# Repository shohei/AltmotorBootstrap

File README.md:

# Altmotor
## Schematics

## Artwork

## Implementation

##Test

## Excitation

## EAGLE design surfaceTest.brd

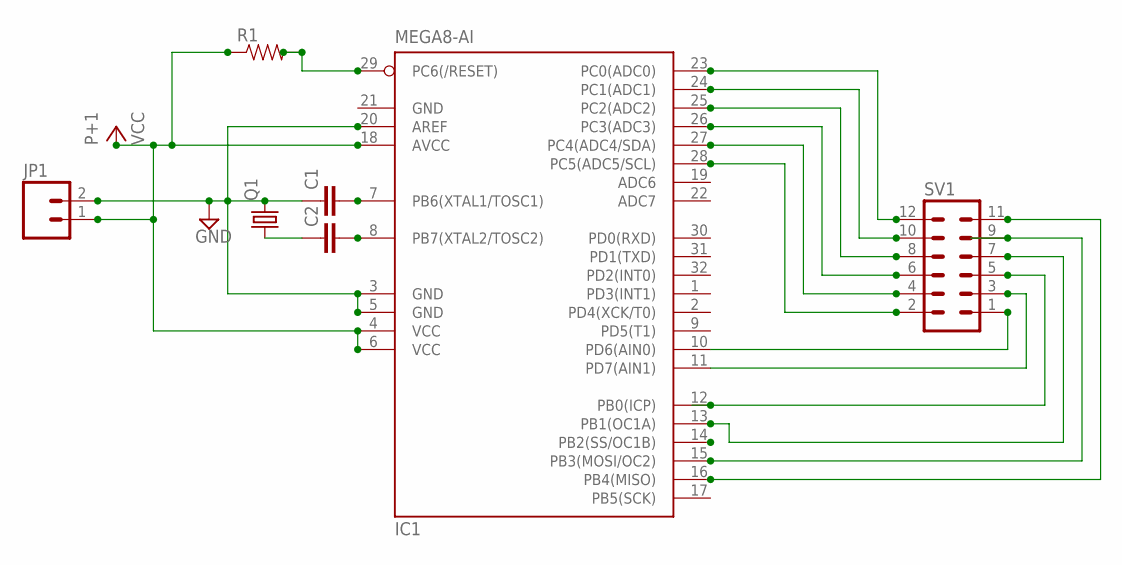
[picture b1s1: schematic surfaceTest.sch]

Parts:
C1, C2: CAPPTH1; CAP-PTH-5MM
IC1: MEGA8-AI; TQFP32-08
JP1: M02LOCK_LONGPADS; 1X02_LOCK_LONGPADS
Q1: CRYSTALHC18U-V; HC18U-V
R1: RESISTORAXIAL-0.3; AXIAL-0.3
SV1: MA06-2

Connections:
GND: C1.1, IC1.3 (GND), IC1.5 (GND), IC1.20 (AREF), IC1.21 (GND), JP1.2, Q1.2
unnamed: C1.2, IC1.7 (PB6(XTAL1/TOSC1))
unnamed: C2.2, IC1.8 (PB7(XTAL2/TOSC2))
unnamed: IC1.25 (PC2(ADC2)), SV1.8
unnamed: C2.1, Q1.1
unnamed: IC1.23 (PC0(ADC0)), SV1.12
unnamed: IC1.24 (PC1(ADC1)), SV1.10
unnamed: IC1.26 (PC3(ADC3)), SV1.6
unnamed: IC1.27 (PC4(ADC4/SDA)), SV1.4
unnamed: IC1.28 (PC5(ADC5/SCL)), SV1.2
unnamed: IC1.10 (PD6(AIN0)), SV1.1
unnamed: IC1.11 (PD7(AIN1)), SV1.3
unnamed: IC1.12 (PB0(ICP)), SV1.5
unnamed: IC1.13 (PB1(OC1A)), SV1.7
unnamed: IC1.15 (PB3(MOSI/OC2)), SV1.9
unnamed: IC1.16 (PB4(MISO)), SV1.11
unnamed: IC1.29 (PC6(/RESET)), R1.P$2 (2)
VCC: IC1.4 (VCC), IC1.6 (VCC), IC1.18 (AVCC), JP1.1, R1.P$1 (1)

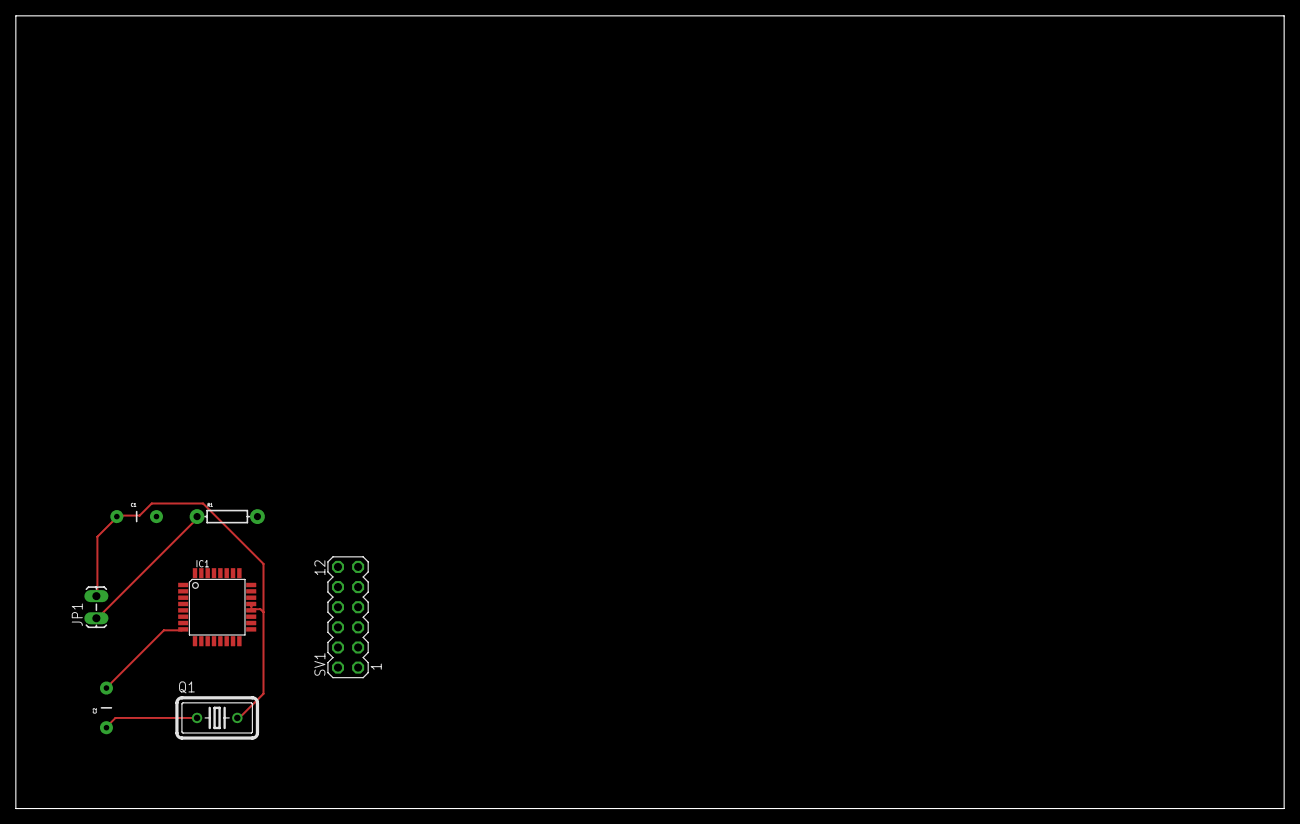
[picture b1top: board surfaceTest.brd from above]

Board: 2 copper layers, 160.0 x 100.0 mm, 7 parts (0 on the bottom side), 18 nets.

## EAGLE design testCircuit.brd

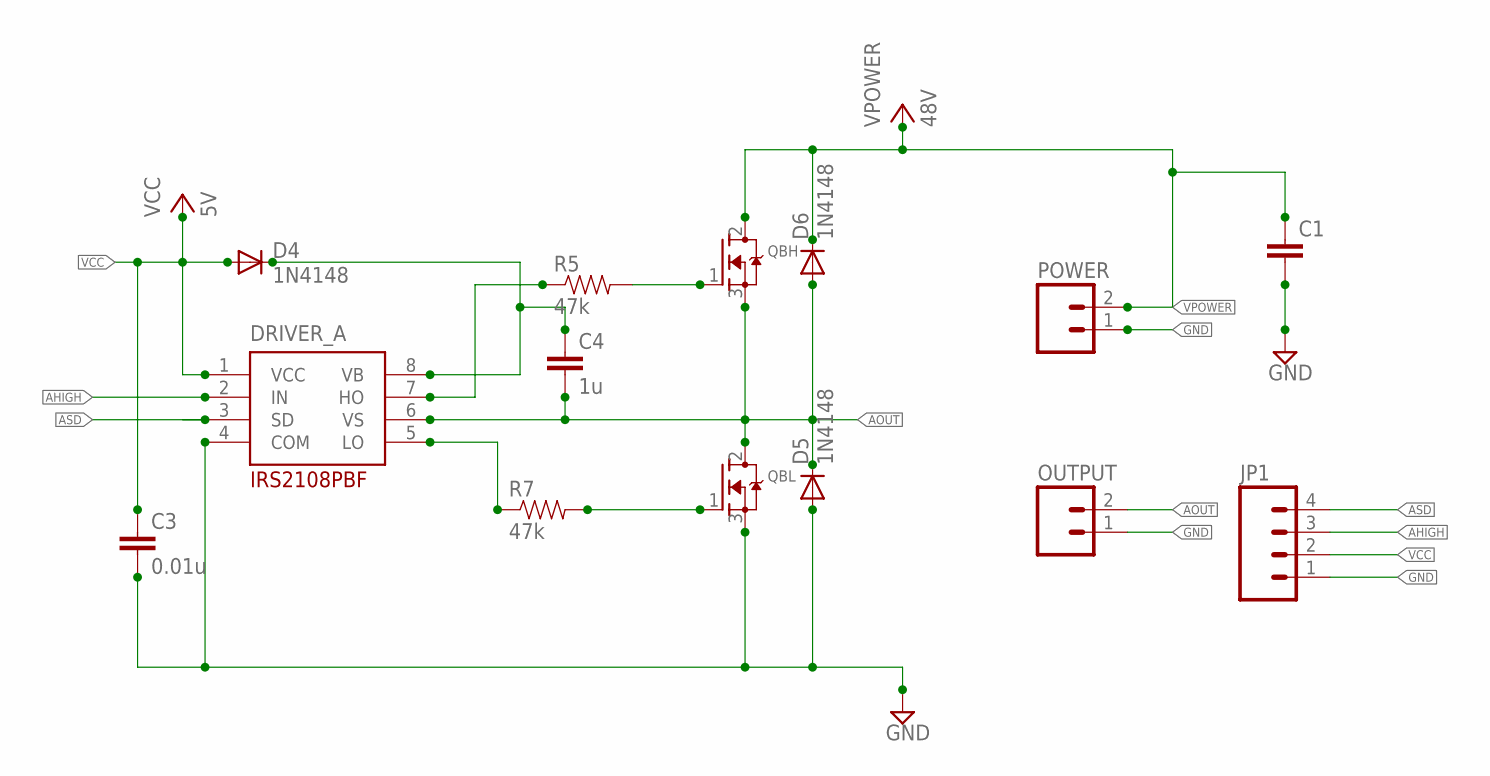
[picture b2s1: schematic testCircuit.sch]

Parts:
C1: CAPPTH1; CAP-PTH-5MM
C3: 0.01u; CAP-PTH-5MM
C4: 1u; CAP-PTH-5MM
D4, D5, D6: 1N4148; DIODE-1N4001
DRIVER_A: IRS2108PBF; DIL08
JP1: M04LONGPADS; 1X04_LONGPADS
OUTPUT: TBLOCK-2
POWER: TBLOCK-2
QBH: MOSFET-NGDS_TO220V; TO220V
QBL: MOSFET-NGDS_TO220V; TO220V
R5, R7: 47k; AXIAL-0.3

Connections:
AHIGH: DRIVER_A.2 (IN), JP1.3
AOUT: C4.2, D5.C, D6.A, DRIVER_A.6 (VS), OUTPUT.2, QBH.3 (S), QBL.2 (D)
ASD: DRIVER_A.3 (SD), JP1.4
GND: C1.2, C3.2, D5.A, DRIVER_A.4 (COM), JP1.1, OUTPUT.1, POWER.1, QBL.3 (S)
unnamed: C4.1, D4.C, DRIVER_A.8 (VB)
unnamed: DRIVER_A.7 (HO), R5.P$1 (1)
unnamed: QBH.1 (G), R5.P$2 (2)
unnamed: DRIVER_A.5 (LO), R7.P$1 (1)
unnamed: QBL.1 (G), R7.P$2 (2)
VCC: C3.1, D4.A, DRIVER_A.1 (VCC), JP1.2
VPOWER: C1.1, D6.C, POWER.2, QBH.2 (D)

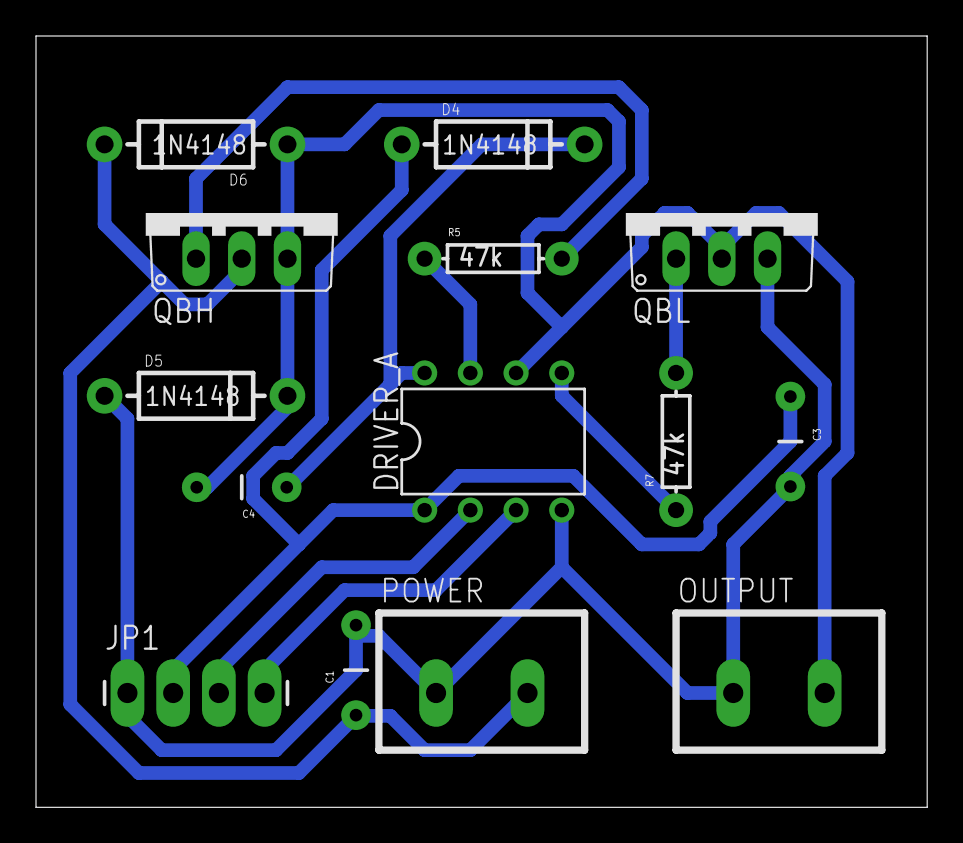
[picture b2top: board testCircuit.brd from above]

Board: 2 copper layers, 49.5 x 42.9 mm, 14 parts (0 on the bottom side), 11 nets.

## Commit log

2016-02-16 remove backup files
2016-02-16 add firmware
2016-02-16 remove test files
2016-02-16 remove unnecessary files
2016-02-16 add readme
2016-02-16 remove temporal files
2016-02-16 add implementation
2016-02-16 remove image
2016-02-16 add youtube link
2016-02-16 add excitation

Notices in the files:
parts and their libraries:
SparkFun: Licensing: CC v3.0 Share-Alike You are welcome to use this library for commercial purposes.
